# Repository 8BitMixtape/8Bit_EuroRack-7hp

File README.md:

# 8Bit_EuroRack-7hp
8Bit Mixtape goes Modular!! Due to popular requests... adapted and improved the mixtape circuit to fit into standard Eurorack Modular format

Join and follow our discussion on the forum:

https://8bitmixtape.discourse.group/t/eurorack-rebooted/47/4

# Features

## 7hp more space for style!

## Two board design

Maybe the Eurorack scene like to have more this kinda standard double-decker style

## 0.1 Prototype - WORKING

### to improve

* Put 2 Neopixel und the potentiometers each
* switch position of Chip and Buttons to create more space between pot and buttons
* optimize position of jacks and pots (sub-millimeter improvements)
* What kinda buttons to use????
* create nice front plates
* anything else?

## Schematic

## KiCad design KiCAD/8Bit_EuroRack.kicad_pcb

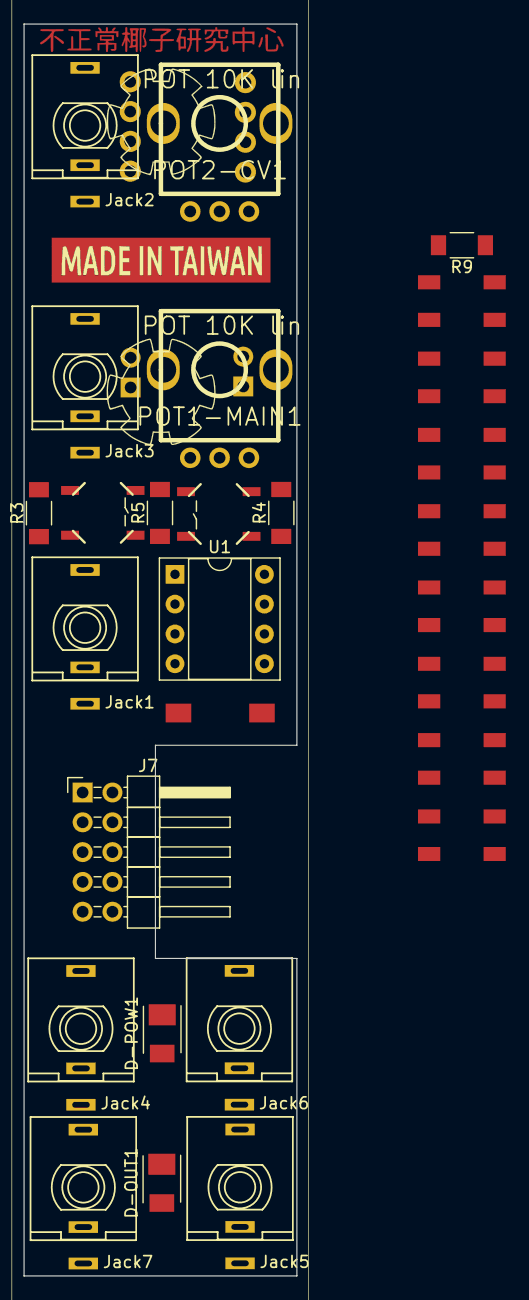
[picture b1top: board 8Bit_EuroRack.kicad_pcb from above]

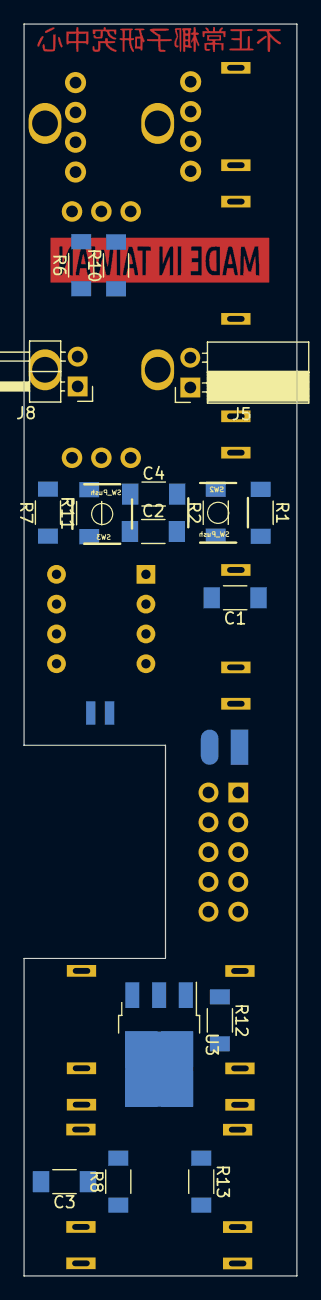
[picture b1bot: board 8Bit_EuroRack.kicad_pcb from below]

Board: 2 copper layers, 23.2 x 106.7 mm, 49 parts (18 on the bottom side), 29 nets, no tracks yet.

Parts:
C1, C2, C3: 100nF; C_1206_3d
C4: 10uF; C_1206_3d
D1, D2, D3, D4, D5, D6, D7, D8: SK6812; Mixtape_NEO_WS2812B_3d
D-OUT1: LED; LED_PLCC_2835_Handsoldering
D-POW1: LED; LED_PLCC_2835_Handsoldering
J1, J2: CONN_01X04; Angled_1x04_Pitch2.54mm-3d
J4: Con_3-5V; Bat_connector_SMD
J5: Conn_01x02; Socket_Strip_Angled_1x02_Pitch2.54mm
J6: Sync_Jumper; Sync_jumper
J7: Conn_02x05_Odd_Even; Pin_Header_Angled_2x05_Pitch2.54mm_with_space_for_con
J8: Conn_01x02; Pin_Header_Angled_1x02_Pitch2.54mm
Jack1, Jack2, Jack3, Jack4, Jack5, Jack6, Jack7: JACK_2P; PJ301M-12_stahl
POT1-MAIN1, POT2-CV1: POT 10K lin; RD901F-ALPHA-3D
R1, R2, R3, R4, R5: 22k; R_1206_3d
R6, R7: 22K; R_1206_3d
R8, R9: 330; R_1206_3d
R10, R11: 4.7K; R_1206_3d
R12, R13: 1K; R_1206_3d
SW2, SW3: SW_Push; TACTILE-SWITCH-SMD
SW4: SW_Push; SW_SPST_FSMSM
U1: ATTINY85-20SU; DIP-8_W7.62mm_Socket
U3: 7805; TO-252-3_TabPin2
board1: SVG2SHENZHEN; 8Bit_EuroRack-NEO

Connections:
+3V3: C2.1, C4.1, D1.3, D2.3, D3.3, D4.3, D5.3, D6.3, D7.3, D8.3, D-POW1.2, J1.3, J2.2, J4.2, R1.1, R10.1, R11.1, U1.8
AudioProg: C1.1, J5.1, Jack1.1
But-L: R3.2, SW2.1
But-R: R4.2, R5.2, SW3.1
CV1_IN: J1.2, Jack2.1, POT2-CV1.1, R10.2
CV2_IN: J5.2, Jack3.1, POT1-MAIN1.1, R11.2
CV_OUT: C3.1, J8.2, Jack5.1, R8.1
DC_in: J7.1, J7.2
GND: C2.2, C3.2, C4.2, D1.1, D2.1, D3.1, D4.1, D5.1, D6.1, D7.1, D8.1, D-OUT1.1, J1.4, J2.1, J4.1, J7.3, J7.4, J7.5, J7.6, J7.7, J7.8, Jack1.3, Jack2.3, Jack3.3, Jack4.3, Jack5.3, Jack6.3, Jack7.3, POT1-MAIN1.3, POT2-CV1.3, R2.2, R12.2, SW2.2, SW3.2, SW4.2, U1.4
unnamed: D1.2, R9.1
unnamed: D1.4, D2.2
unnamed: D2.4, D3.2
unnamed: D3.4, D4.2
unnamed: D4.4, D5.2
unnamed: D5.4, D6.2
unnamed: D6.4, D7.2
unnamed: D7.4, D8.2
unnamed: D-OUT1.2, R13.2
unnamed: D-POW1.1, R12.1
unnamed: J6.1, SW4.1, U1.1
unnamed: J7.9, J7.10
unnamed: POT1-MAIN1.2, R7.2
unnamed: POT2-CV1.2, R6.2
PB0: J8.1, Jack7.1, R9.2, U1.5
PB1: J2.3, R8.2, R13.1, U1.6
PB2/A1: R7.1, U1.7
PB4/A2: R6.1, U1.3
Sync_IN: C1.2, J1.1, Jack4.1, R1.2, R2.1, R3.1, R4.1, R5.1, U1.2
Sync_OUT: J2.4, J6.2, Jack6.1

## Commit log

2019-05-15 all files for v0.v0.1
2019-05-15 writing a bit more on readme
2019-05-16 frontplate designs
2019-05-30 adding new 3d files for case
2019-06-02 small changes on case
